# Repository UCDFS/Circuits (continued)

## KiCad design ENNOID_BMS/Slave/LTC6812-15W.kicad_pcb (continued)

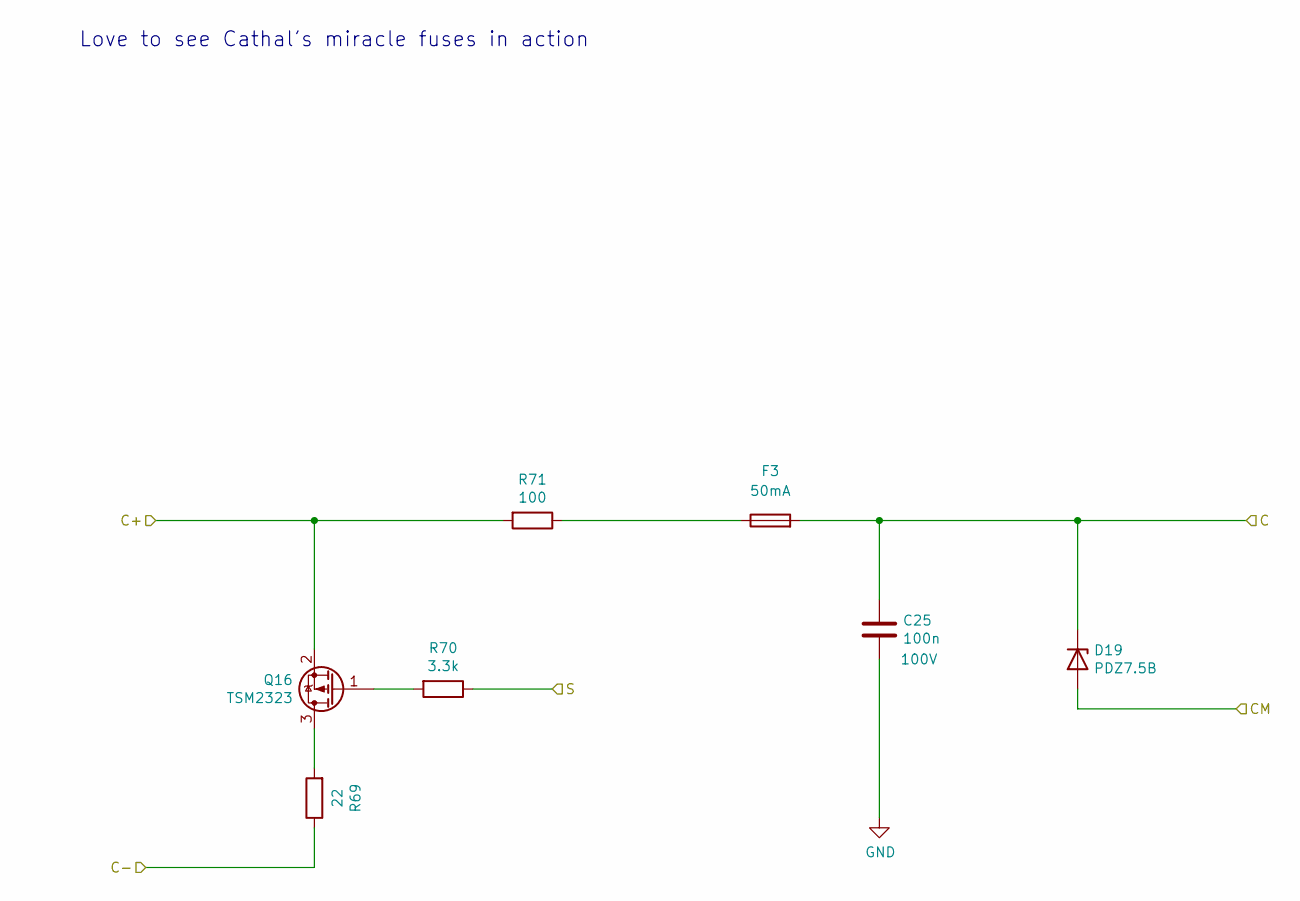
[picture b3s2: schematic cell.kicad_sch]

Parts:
C25: 100n; C_0603_1608Metric; Voltage 100V; Part Number GRM188R72A104KA35D
D19: PDZ7.5B; D_SOD-323; Part Number PDZ7.5B
F3: 50mA; Fuse_1206_3216Metric; Part Number 3413.0002.11
Q16: TSM2323; SOT-23; Part Number TSM2323CX RFG
R69: 22; R_2512_6332Metric; Part Number AC2512JK-7W22RL
R70: 3.3k; R_0508_1220Metric; Part Number WK73R2ATTD3301F
R71: 100; R_0603_1608Metric; Part Number RCS0603100RFKEA

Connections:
/cell14/C: D19.2 (A); also elsewhere on the board
/cell15/C: C25.2, D19.1 (K), F3.2; also elsewhere on the board
/cell15/S: R70.1; also elsewhere on the board
Cell_1-: C25.1; also elsewhere on the board
Cell_14+: R69.1; also elsewhere on the board
Cell_15+: Q16.2 (S), R71.2; also elsewhere on the board
unnamed: F3.1, R71.1
unnamed: Q16.3 (D), R69.2
unnamed: Q16.1 (G), R70.2

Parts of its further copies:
C11, C12, C13, C14, C15, C16, C17, C18, C19, C20, C21, C22, C23, C24: 100n; C_0603_1608Metric; Voltage 100V; Part Number GRM188R72A104KA35D
D5, D6, D7, D8, D9, D10, D11, D12, D13, D14, D15, D16, D17, D18: PDZ7.5B; D_SOD-323; Part Number PDZ7.5B
F5, F7, F9, F11, F13, F15, F20, F22, F24, F26, F28, F30, F32, F34: 50mA; Fuse_1206_3216Metric; Part Number 3413.0002.11
Q2, Q3, Q4, Q5, Q6, Q7, Q8, Q9, Q10, Q11, Q12, Q13, Q14, Q15: TSM2323; SOT-23; Part Number TSM2323CX RFG
R13, R17, R21, R25, R29, R33, R37, R41, R45, R49, R53, R57, R61, R65: 22; R_2512_6332Metric; Part Number AC2512JK-7W22RL
R14, R18, R22, R26, R30, R34, R38, R42, R46, R50, R54, R58, R62, R66: 3.3k; R_0508_1220Metric; Part Number WK73R2ATTD3301F
R15, R19, R23, R27, R31, R35, R39, R43, R47, R51, R55, R59, R63, R67: 100; R_0603_1608Metric; Part Number RCS0603100RFKEA

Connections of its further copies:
/cell1/C: C11.2, D5.1 (K), D6.2 (A), F34.2; also elsewhere on the board
/cell1/S: R14.1; also elsewhere on the board
/cell2/C: C12.2, D6.1 (K), D7.2 (A), F32.2; also elsewhere on the board
/cell2/S: R18.1; also elsewhere on the board
/cell3/C: C13.2, D7.1 (K), D8.2 (A), F30.2; also elsewhere on the board
/cell3/S: R22.1; also elsewhere on the board
/cell4/C: C14.2, D8.1 (K), D9.2 (A), F28.2; also elsewhere on the board
/cell4/S: R26.1; also elsewhere on the board
/cell5/C: C15.2, D9.1 (K), D10.2 (A), F26.2; also elsewhere on the board
/cell5/S: R30.1; also elsewhere on the board
/cell6/C: C16.2, D10.1 (K), D11.2 (A), F24.2; also elsewhere on the board
/cell6/S: R34.1; also elsewhere on the board
/cell7/C: C17.2, D11.1 (K), D12.2 (A), F22.2; also elsewhere on the board
/cell7/S: R38.1; also elsewhere on the board
/cell8/C: C18.2, D12.1 (K), D13.2 (A), F20.2; also elsewhere on the board
/cell8/S: R42.1; also elsewhere on the board
/cell9/S: R46.1; also elsewhere on the board
/cell10/C: C20.2, D14.1 (K), D15.2 (A), F13.2; also elsewhere on the board
/cell10/CM: C19.2, D13.1 (K), D14.2 (A), F15.2; also elsewhere on the board
/cell10/S: R50.1; also elsewhere on the board
/cell11/C: C21.2, D15.1 (K), D16.2 (A), F11.2; also elsewhere on the board
/cell11/S: R54.1; also elsewhere on the board
/cell12/C: C22.2, D16.1 (K), D17.2 (A), F9.2; also elsewhere on the board
/cell12/S: R58.1; also elsewhere on the board
/cell13/C: C23.2, D17.1 (K), D18.2 (A), F7.2; also elsewhere on the board
/cell13/S: R62.1; also elsewhere on the board
/cell14/C: C24.2, D18.1 (K), F5.2; also elsewhere on the board
/cell14/S: R66.1; also elsewhere on the board
Cell_1+: Q2.2 (S), R15.2, R17.1; also elsewhere on the board
Cell_1-: C11.1, C12.1, C13.1, C14.1, C15.1, C16.1, C17.1, C18.1, C19.1, C20.1, C21.1, C22.1, C23.1, C24.1, D5.2 (A), R13.1; also elsewhere on the board
Cell_2+: Q3.2 (S), R19.2, R21.1; also elsewhere on the board
Cell_3+: Q4.2 (S), R23.2, R25.1; also elsewhere on the board
Cell_4+: Q5.2 (S), R27.2, R29.1; also elsewhere on the board
Cell_5+: Q6.2 (S), R31.2, R33.1; also elsewhere on the board
Cell_6+: Q7.2 (S), R35.2, R37.1; also elsewhere on the board
Cell_7+: Q8.2 (S), R39.2, R41.1; also elsewhere on the board
Cell_8+: Q9.2 (S), R43.2, R45.1; also elsewhere on the board
Cell_9+: Q10.2 (S), R47.2, R49.1; also elsewhere on the board
Cell_10+: Q11.2 (S), R51.2, R53.1; also elsewhere on the board
Cell_11+: Q12.2 (S), R55.2, R57.1; also elsewhere on the board
Cell_12+: Q13.2 (S), R59.2, R61.1; also elsewhere on the board
Cell_13+: Q14.2 (S), R63.2, R65.1; also elsewhere on the board
Cell_14+: Q15.2 (S), R67.2; also elsewhere on the board
unnamed: F5.1, R67.1
unnamed: F7.1, R63.1
unnamed: F9.1, R59.1
unnamed: F11.1, R55.1
unnamed: F13.1, R51.1
unnamed: F15.1, R47.1
unnamed: F20.1, R43.1
unnamed: F22.1, R39.1
unnamed: F24.1, R35.1
unnamed: F26.1, R31.1
unnamed: F28.1, R27.1
unnamed: F30.1, R23.1
unnamed: F32.1, R19.1
unnamed: F34.1, R15.1
unnamed: Q2.3 (D), R13.2
unnamed: Q2.1 (G), R14.2
unnamed: Q3.3 (D), R17.2
unnamed: Q3.1 (G), R18.2
unnamed: Q4.3 (D), R21.2
unnamed: Q4.1 (G), R22.2
unnamed: Q5.3 (D), R25.2
unnamed: Q5.1 (G), R26.2
unnamed: Q6.3 (D), R29.2
unnamed: Q6.1 (G), R30.2
unnamed: Q7.3 (D), R33.2
unnamed: Q7.1 (G), R34.2
unnamed: Q8.3 (D), R37.2
unnamed: Q8.1 (G), R38.2
unnamed: Q9.3 (D), R41.2
unnamed: Q9.1 (G), R42.2
unnamed: Q10.3 (D), R45.2
unnamed: Q10.1 (G), R46.2
unnamed: Q11.3 (D), R49.2
unnamed: Q11.1 (G), R50.2
unnamed: Q12.3 (D), R53.2
unnamed: Q12.1 (G), R54.2
unnamed: Q13.3 (D), R57.2
unnamed: Q13.1 (G), R58.2
unnamed: Q14.3 (D), R61.2
unnamed: Q14.1 (G), R62.2
unnamed: Q15.3 (D), R65.2
unnamed: Q15.1 (G), R66.2

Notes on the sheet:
Love to see Cathal's miracle fuses in action

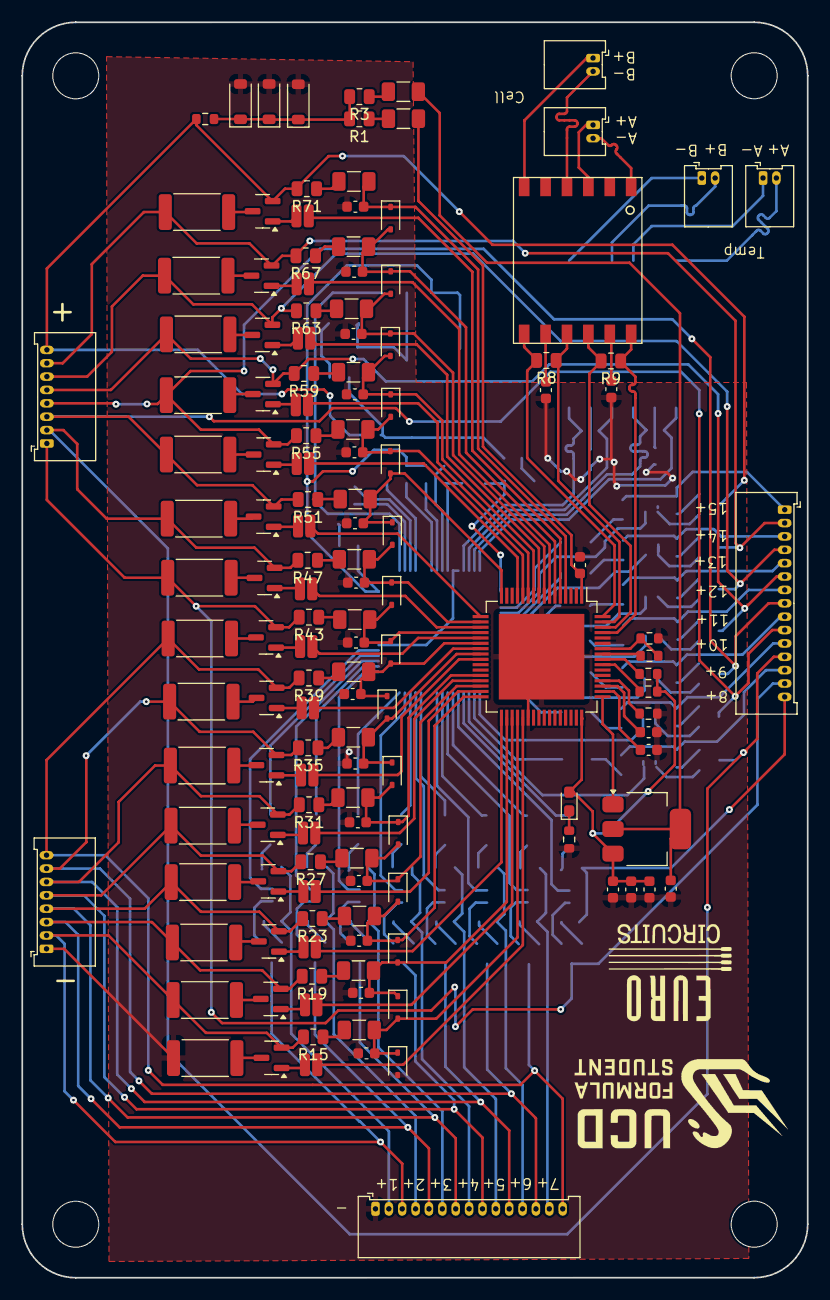
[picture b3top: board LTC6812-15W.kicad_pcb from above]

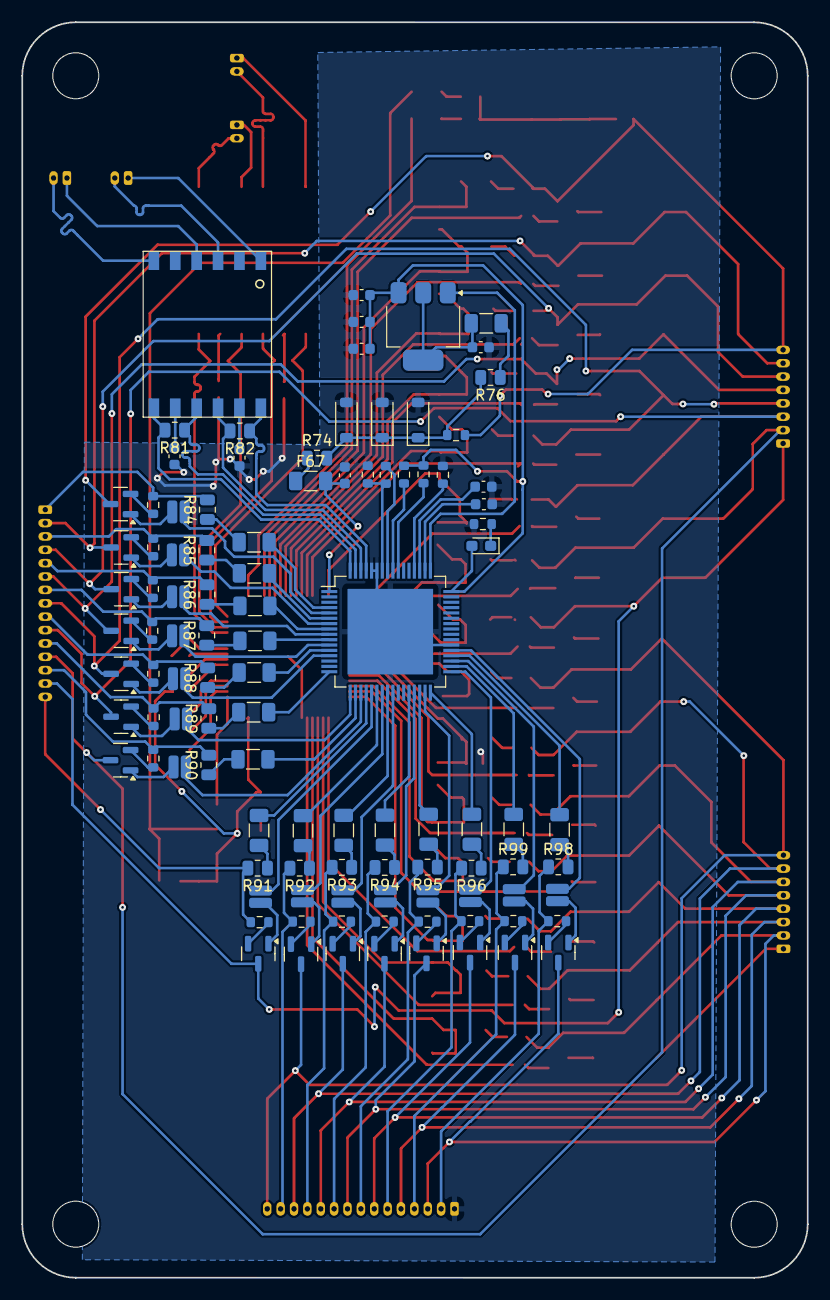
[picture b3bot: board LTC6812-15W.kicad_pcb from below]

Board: 2 copper layers, 73.4 x 117.4 mm, 246 parts (104 on the bottom side), 231 nets.

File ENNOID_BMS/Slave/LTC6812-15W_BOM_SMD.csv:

Reference,Qty,Value,DNP,Exclude from Board,Footprint,Datasheet,Part Number
"C1,C4,C10,C11,C12,C13,C14,C15,C16,C17,C18,C19,C20,C21,C22,C23,C24,C25,C28",19,100n,,,Capacitor_SMD:C_0603_1608Metric,https://pim.murata.com/asset/pim4/ceramicCapacitorSMD/GRM188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,GRM188R72A104KA35D
"C2,C3,C5,C6,C7,C26,C27,C29,C30,C31",10,1uF,,,Capacitor_SMD:C_0603_1608Metric,https://mm.digikey.com/Volume0/opasdata/d220001/medias/docus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,CL10B105KP8NNNC
"C8,C9,C32,C33",4,100p,,,Capacitor_SMD:C_0603_1608Metric,https://pim.murata.com/asset/pim4/ceramicCapacitorSMD/GRM188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,GRM1885C1H101JA01D
"D1,D2,D20,D21",4,1N4148W,,,Diode_SMD:D_SOD-123,https://www.mouser.ie/datasheet/3/175/1/BAV16W_1N4148W.pdf,1N4148W-7-F
"D3,D22",2,MMSZ5268BT1G,,,Diode_SMD:D_SOD-123,https://www.onsemi.com/pub/Collateral/MMSZ5221BT1-D.PDF,MMSZ5268BT1G
"D4,D23",2,LED,,,LED_SMD:LED_0603_1608Metric_Pad1.05x0.95mm_HandSolder,https://www.vishay.com/doc?84393,VLMTG1400-GS08
"D5,D6,D7,D8,D9,D10,D11,D12,D13,D14,D15,D16,D17,D18,D19",15,PDZ7.5B,,,Diode_SMD:D_SOD-323,https://assets.nexperia.com/documents/data-sheet/PDZ-B_SER.pdf,PDZ7.5B
"F4,F5,F6,F7,F8,F9,F10,F11,F12,F13,F14,F15,F16,F17,F18,F19",16,0.25A,,,Fuse:Fuse_0603_1608Metric,https://www.littelfuse.com/assetdocs/littelfuse_fuse_438_dat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,0438.250WR
"FB1,FB2",2,33,,,Resistor_SMD:R_0603_1608Metric,https://www.mouser.ie/datasheet/3/76/1/ENFA0003.pdf,BLM18PG330SN1D
"Q1,Q17",2,DZTT5551,,,Package_TO_SOT_SMD:SOT-223,https://www.mouser.ie/datasheet/3/175/1/ds31219.pdf,DZT5551-13
"Q2,Q3,Q4,Q5,Q6,Q7,Q8,Q9,Q10,Q11,Q12,Q13,Q14,Q15,Q16",15,TSM2323,,,Package_TO_SOT_SMD:SOT-23,https://www.taiwansemi.com/assets/datasheet/pdf.php?pn=TSM2323CX,TSM2323
"R1,R3,R8,R9,R15,R19,R23,R27,R31,R35,R39,R43,R47,R51,R55,R59,R63,R67,R71,R74,R76,R81,R82,R84,R85,R86,R87,R88,R89,R90,R91,R92,R93,R94,R95,R96,R98,R99",38,100,,,Resistor_SMD:R_0603_1608Metric,https://www.vishay.com/docs/20035/dcrcwe3.pdf,CRCW0603100RFKEA
"R2,R75",2,806,,,Resistor_SMD:R_0603_1608Metric,https://www.vishay.com/docs/20035/dcrcwe3.pdf,CRCW0603806RFKEA
"R4,R77",2,1M,,,Resistor_SMD:R_0603_1608Metric,https://www.vishay.com/docs/20035/dcrcwe3.pdf,CRCW06031M00FKEA
"R5,R10,R78,R83",4,1.2k,,,Resistor_SMD:R_0603_1608Metric,https://www.vishay.com/docs/20035/dcrcwe3.pdf,CRCW06031K20FKEA
"R6,R7,R79,R80",4,0,,,Resistor_SMD:R_0603_1608Metric,https://www.vishay.com/docs/20035/dcrcwe3.pdf,CRCW06030000Z0EA
"R11,R12,R16,R20,R24,R28,R32,R36,R40,R44,R48,R52,R56,R60,R64",15,680,,,Resistor_SMD:R_0603_1608Metric,https://www.vishay.com/docs/20035/dcrcwe3.pdf,CRCW0603680RFKEA
"R13,R17,R21,R25,R29,R33,R37,R41,R45,R49,R53,R57,R61,R65,R69",15,22,,,Resistor_SMD:R_2512_6332Metric,https://www.mouser.ie/datasheet/3/508/1/PYu-AC_51_RoHS_L_11.pdf,AC2512JK-7W22RL
"R14,R18,R22,R26,R30,R34,R38,R42,R46,R50,R54,R58,R62,R66,R70",15,3.3k,,,Resistor_SMD:R_0603_1608Metric,https://www.vishay.com/docs/20035/dcrcwe3.pdf,CRCW06033K30FKEA
"TR1,TR2",2,HM2102NL,,,ENNOID:HM2102NL,https://www.mouser.ie/datasheet/3/508/1/HM2102NL.pdf,HM2102NL
"U1,U2",2,LTC6812-1,,,ENNOID:TQFP-64-1EP_10x10mm_P0.5mm_EP8x8mm,https://www.analog.com/media/en/technical-documentation/data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,LTC6812-1

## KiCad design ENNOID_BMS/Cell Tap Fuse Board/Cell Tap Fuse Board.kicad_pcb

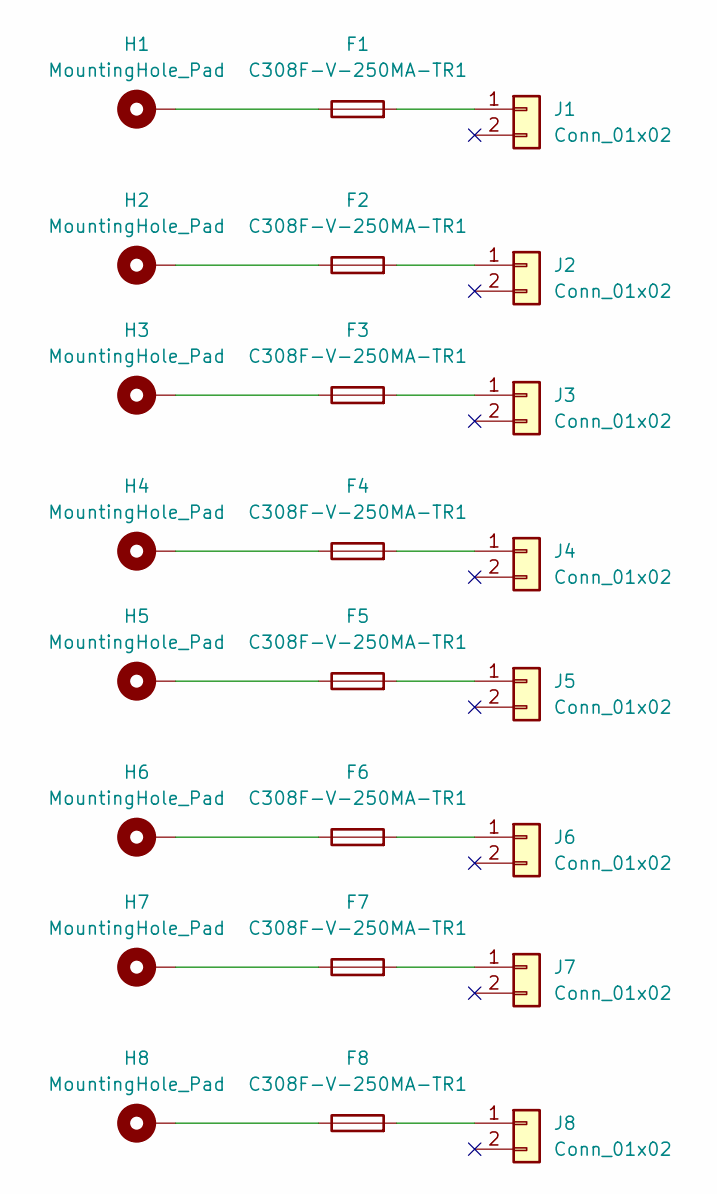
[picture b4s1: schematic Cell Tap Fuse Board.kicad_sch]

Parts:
F1, F2, F3, F4, F5, F6, F7, F8: C308F-V-250MA-TR1; MPN C308F-V-250MA-TR1
H1, H2, H3, H4, H5, H6, H7, H8: MountingHole_Pad; MountingHole_5.5mm_Pad
J1, J2, J3, J4, J5, J6, J7, J8: Conn_01x02; Molex_PicoBlade_53047-0210_1x02_P1.25mm_Vertical; MPN 53047-0210

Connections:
unnamed: F1.1, H1.1
unnamed: F2.1, H2.1
unnamed: F3.1, H3.1
unnamed: F4.1, H4.1
unnamed: F5.1, H5.1
unnamed: F6.1, H6.1
unnamed: F7.1, H7.1
unnamed: F8.1, H8.1
unnamed: F1.2, J1.1
unnamed: F2.2, J2.1
unnamed: F3.2, J3.1
unnamed: F4.2, J4.1
unnamed: F5.2, J5.1
unnamed: F6.2, J6.1
unnamed: F7.2, J7.1
unnamed: F8.2, J8.1

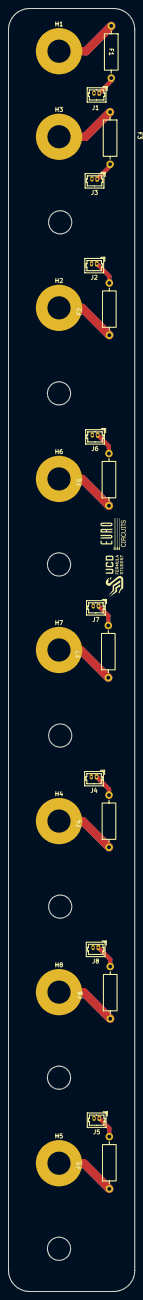
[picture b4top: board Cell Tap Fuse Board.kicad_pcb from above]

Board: 2 copper layers, 30.0 x 304.9 mm, 24 parts (0 on the bottom side), 16 nets.

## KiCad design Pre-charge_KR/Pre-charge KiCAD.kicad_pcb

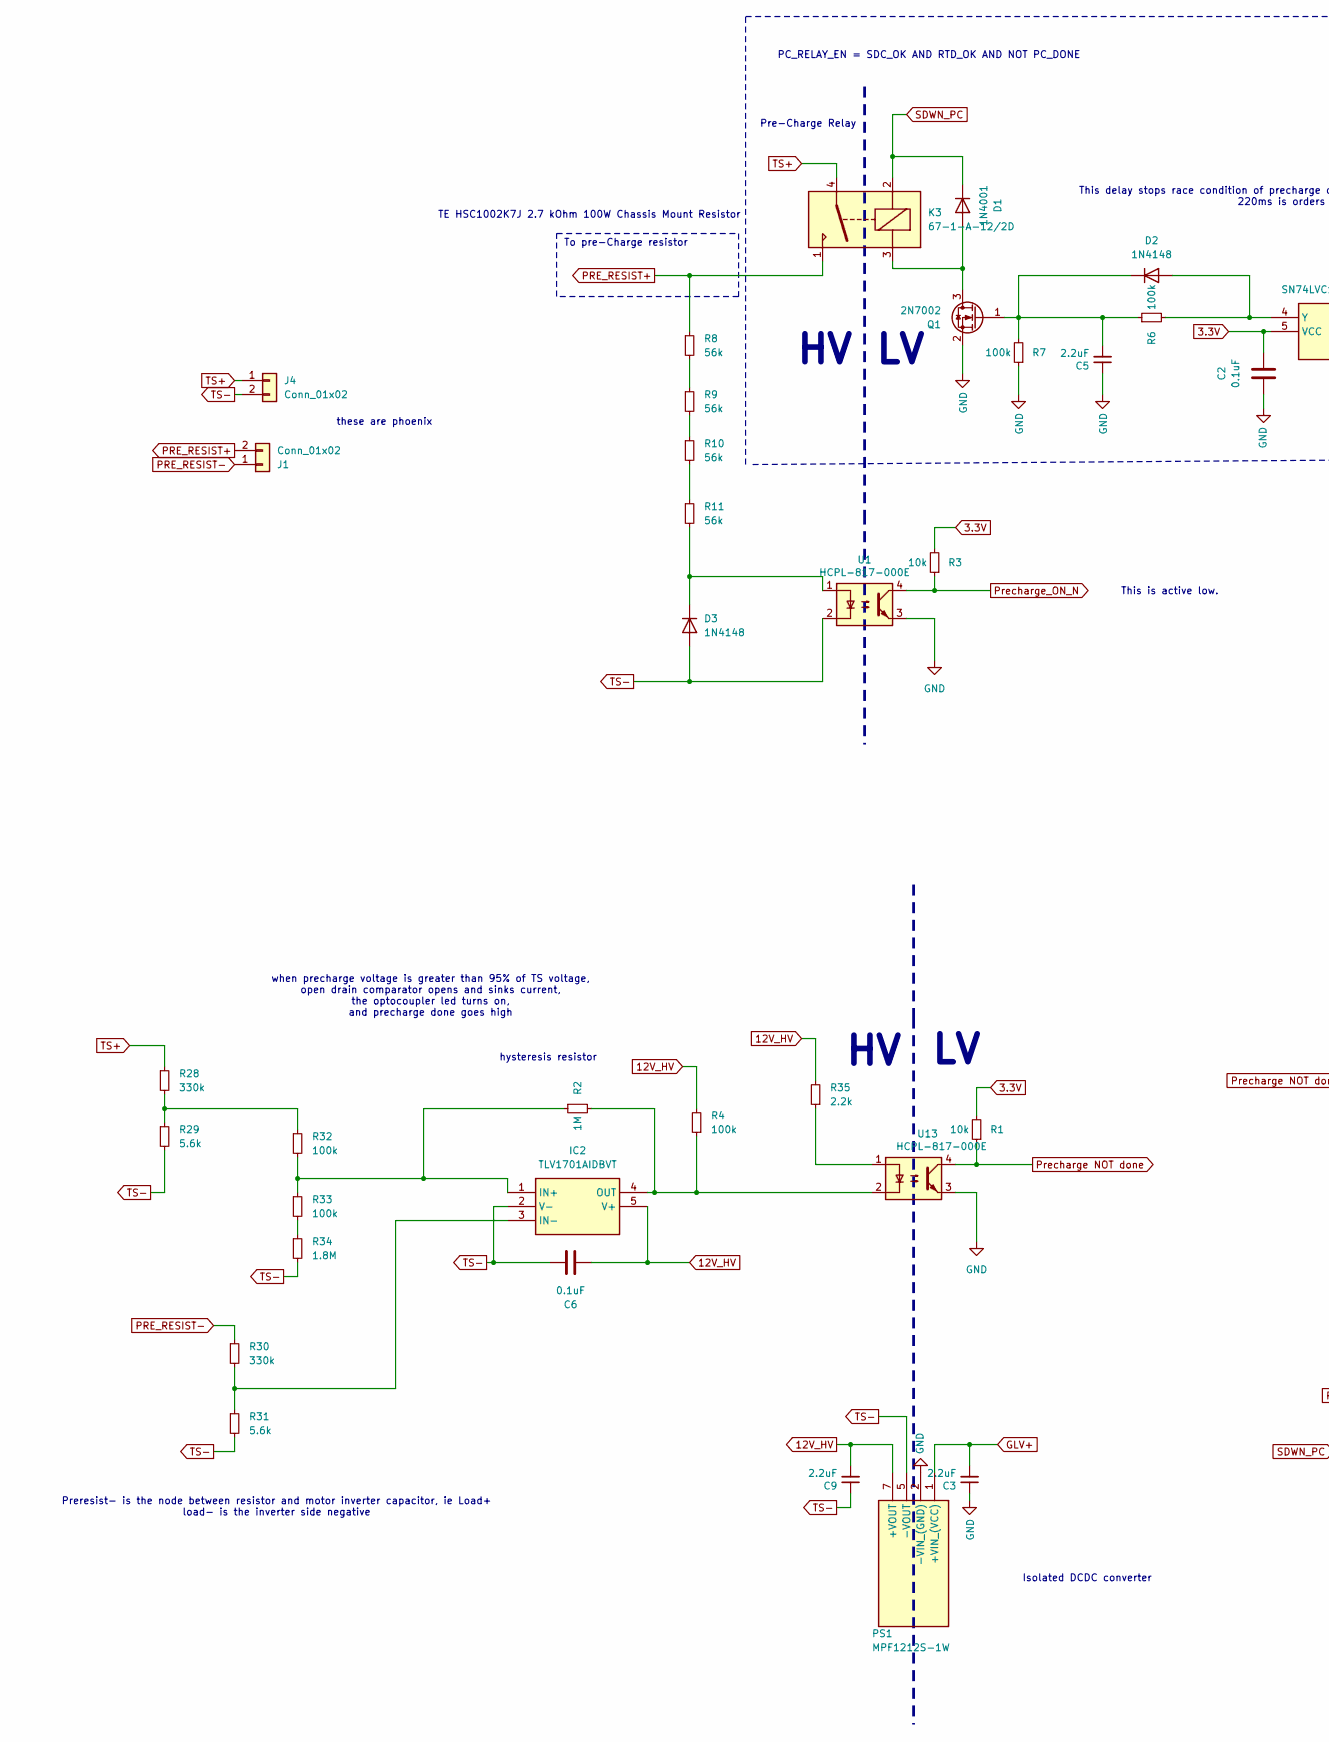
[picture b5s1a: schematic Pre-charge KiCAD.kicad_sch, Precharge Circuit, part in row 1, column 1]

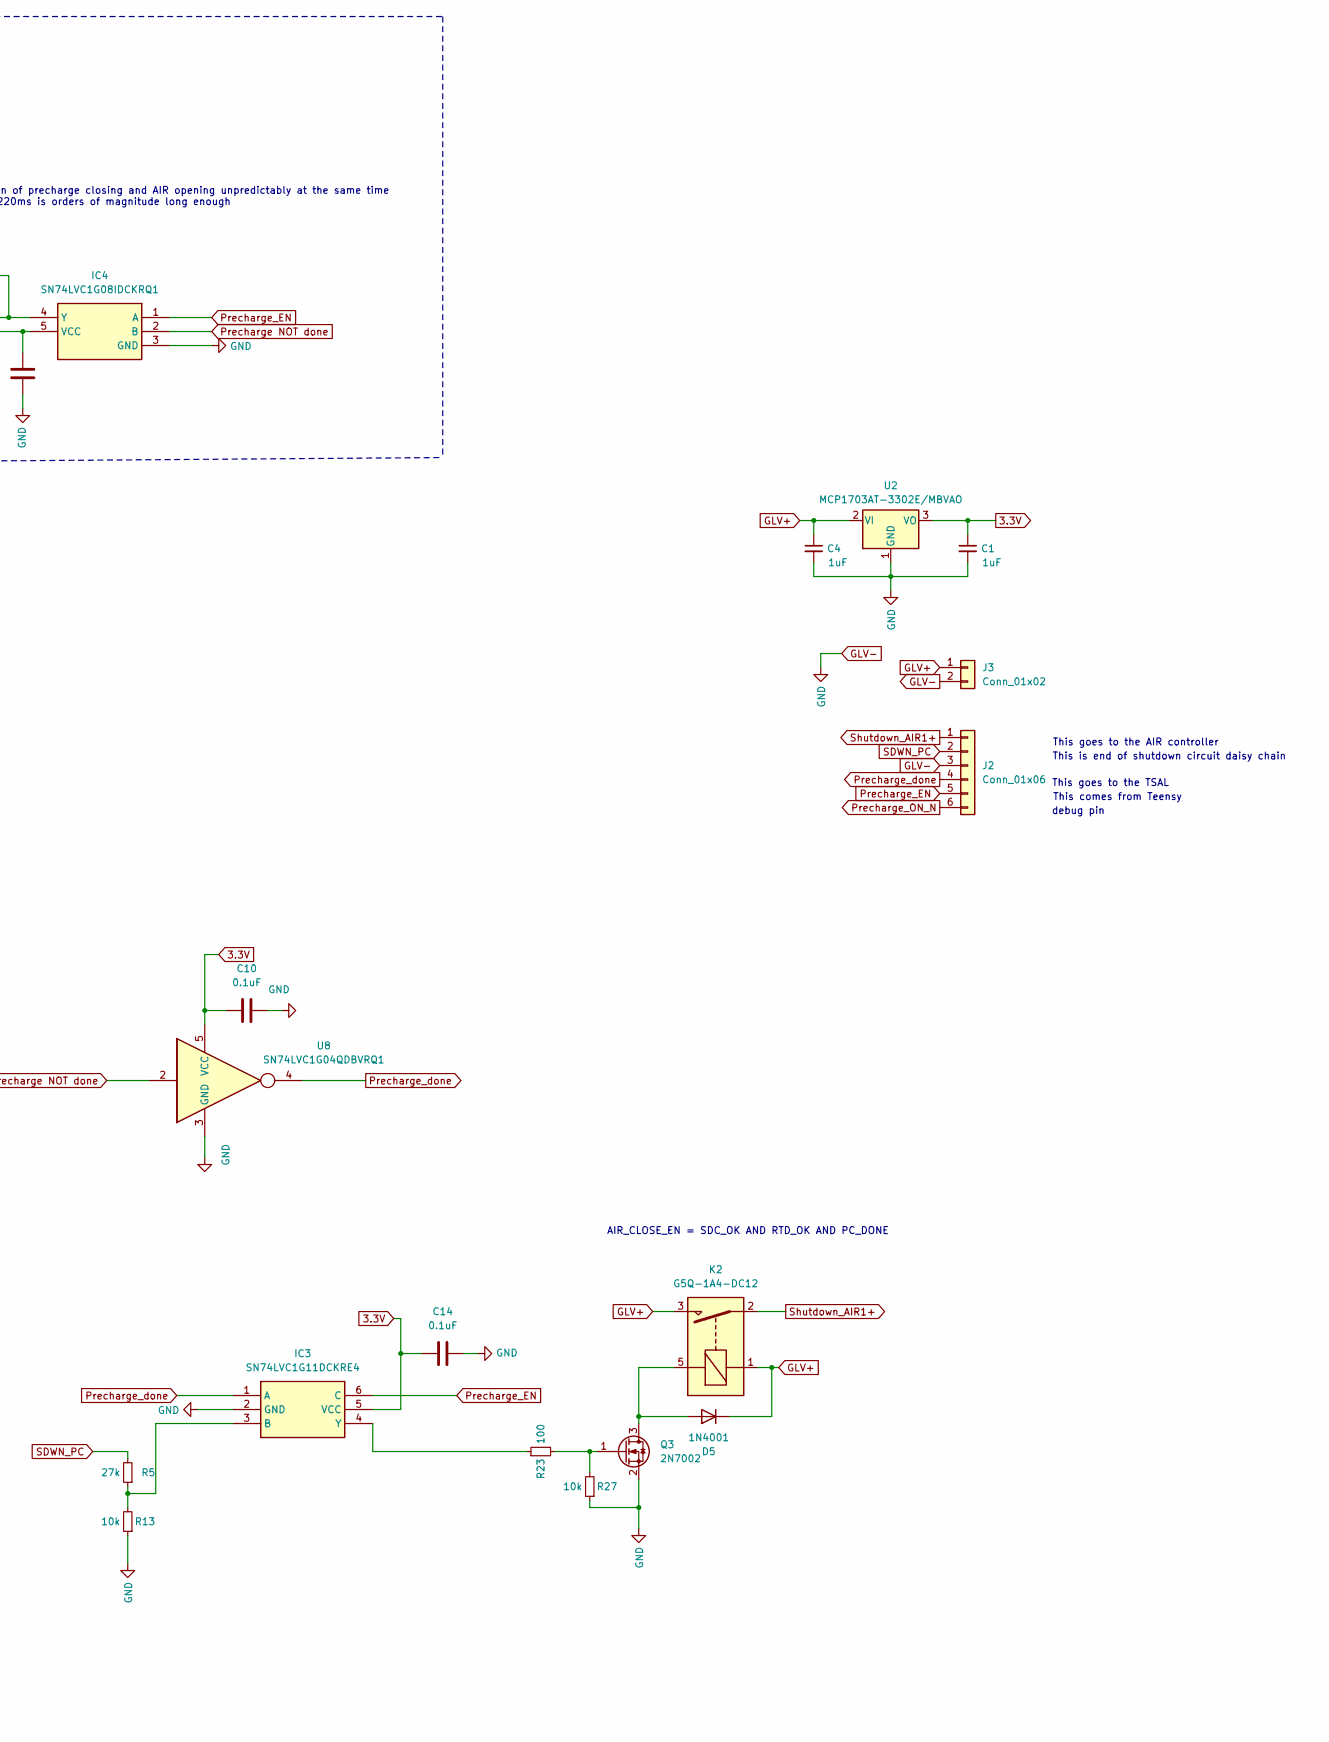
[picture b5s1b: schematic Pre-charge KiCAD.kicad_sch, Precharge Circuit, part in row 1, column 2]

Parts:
C1, C4: 1uF; FA18X7R1H104KNU00; Part Number FA18X7R1E105KRU00
C2, C6, C10, C14: 0.1uF; FA18X7R1H104KNU00; Part Number FA18X7R1H104KNU00
C3, C5, C9: 2.2uF; FA14X7R1H224KNU00; Part Number FA14X7R1H225KRU00
D1, D5: 1N4001; D_DO-41_SOD81_P10.16mm_Horizontal; Part Number 1N4001
D2, D3: 1N4148; D_DO-35_SOD27_P7.62mm_Horizontal; Part Number 1N4148
IC2: TLV1701AIDBVT; SOT95P280X145-5N; Mouser Part Number 595-TLV1701AIDBVT
IC3: SN74LVC1G11DCKRE4; SOT65P210X110-6N; Mouser Part Number 595-74LVC1G11DCKRE4
IC4: SN74LVC1G08IDCKRQ1; SOT65P210X110-5N; Mouser Part Number 595-SN74LVC1G08IDCQ1
J1, J4: Conn_01x02; Phoenix_1x2_1729128; Part Number 1729128
J2: Conn_01x06; JST_XH_B6B-XH-A_1x06_P2.50mm_Vertical; Part Number B6B-XH-A
J3: Conn_01x02; JST_XH_B2B-XH-A_1x02_P2.50mm_Vertical; Part Number B2B-XH-A
K2: G5Q-1A4-DC12; Relay_SPST_Omron-G5Q-1A; Part Number G5Q-1A4-DC12
K3: 67-1-A-12/2D; 67-1-A-12_2D; Part Number 67-1-A-12/2D
PS1: MPF1212S-1W; Part Number MPF1212S-1W
Q1, Q3: 2N7002; SOT-23; Part Number 2N7002
R1, R3, R13, R27: 10k; R_Axial_DIN0207_L6.3mm_D2.5mm_P10.16mm_Horizontal; Part Number MCF 0.25W 10K
R2: 1M; R_Axial_DIN0207_L6.3mm_D2.5mm_P10.16mm_Horizontal; Part Number MCF 0.25W 1M
R4, R6, R7, R32, R33: 100k; R_Axial_DIN0207_L6.3mm_D2.5mm_P10.16mm_Horizontal; Part Number MCF 0.25W 100K
R5: 27k; R_Axial_DIN0207_L6.3mm_D2.5mm_P10.16mm_Horizontal; Part Number MCF 0.25W 27K
R8, R9, R10, R11: 56k; R_Axial_DIN0411_L9.9mm_D3.6mm_P12.70mm_Horizontal; Part Number MCF 0.5W 56K
R23: 100; R_Axial_DIN0207_L6.3mm_D2.5mm_P10.16mm_Horizontal; Part Number MCF 0.25W 100R
R28, R30: 330k; R_Axial_DIN0411_L9.9mm_D3.6mm_P12.70mm_Horizontal; Part Number MCF 0.5W 330K
R29, R31: 5.6k; R_Axial_DIN0207_L6.3mm_D2.5mm_P10.16mm_Horizontal; Part Number MCF 0.25W 5K6
R34: 1.8M; R_Axial_DIN0207_L6.3mm_D2.5mm_P10.16mm_Horizontal; Part Number MCF 0.25W 1.8M
R35: 2.2k; R_Axial_DIN0207_L6.3mm_D2.5mm_P10.16mm_Horizontal; Part Number MCF 0.25W 2.2k
U1, U13: HCPL-817-000E; DIP-4_W7.62mm; Part Number HCPL-817-000E
U2: MCP1703AT-3302E/MBVAO; SOT-89-3; Part Number MCP1703AT-3302E/MBVAO
U8: SN74LVC1G04QDBVRQ1; SOT-23-5; Part Number SN74LVC1G04QDBVRQ1

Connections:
3.3V: C1.1, C2.1, C10.1, C14.1, IC3.5 (VCC), IC4.5 (VCC), R1.2, R3.2, U2.3 (VO), U8.5 (VCC)
12V_HV: C6.1, C9.2, IC2.5 (V+), PS1.7 (+VOUT), R4.2, R35.2
GLV+: C3.2, C4.1, D5.1 (K), J3.1, K2.1, K2.3, PS1.1 (+VIN_(VCC)), U2.2 (VI)
GLV-: C1.2, C2.2, C3.1, C4.2, C5.1, C10.2, C14.2, IC3.2 (GND), IC4.3 (GND), J2.3, J3.2, PS1.2 (-VIN_(GND)), Q1.2 (S), Q3.2 (S), R7.1, R13.1, R27.1, U1.3, U2.1 (GND), U8.3 (GND), U13.3
unnamed: D1.2 (A), K3.3, Q1.3 (D)
unnamed: D2.2 (A), IC4.4 (Y), R6.2
unnamed: C5.2, D2.1 (K), Q1.1 (G), R6.1, R7.2
unnamed: D3.1 (K), R11.2, U1.1
unnamed: D5.2 (A), K2.5, Q3.3 (D)
unnamed: IC2.1 (IN+), R2.1, R32.2, R33.1
unnamed: IC2.3 (IN-), R30.2, R31.1
unnamed: IC2.4 (OUT), R2.2, R4.1, U13.2
unnamed: IC3.3 (B), R5.1, R13.2
unnamed: IC3.4 (Y), R23.1
unnamed: Q3.1 (G), R23.2, R27.2
unnamed: R8.2, R9.1
unnamed: R9.2, R10.1
unnamed: R10.2, R11.1
unnamed: R28.2, R29.1, R32.1
unnamed: R33.2, R34.1
unnamed: R35.1, U13.1
PRE_RESIST+: J1.2, K3.1, R8.1
PRE_RESIST-: J1.1, R30.1
Precharge NOT done: IC4.2 (B), R1.1, U8.2, U13.4
Precharge_EN: IC3.6 (C), IC4.1 (A), J2.5
Precharge_ON_N: J2.6, R3.1, U1.4
Precharge_done: IC3.1 (A), J2.4, U8.4
SDWN_PC: D1.1 (K), J2.2, K3.2, R5.2
Shutdown_AIR1+: J2.1, K2.2
TS+: J4.1, K3.4, R28.1
TS-: C6.2, C9.1, D3.2 (A), IC2.2 (V-), J4.2, PS1.5 (-VOUT), R29.2, R31.2, R34.2, U1.2

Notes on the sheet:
This is end of shutdown circuit daisy chain
This goes to the TSAL
PC_RELAY_EN = SDC_OK AND RTD_OK AND NOT PC_DONE
This comes from Teensy
AIR_CLOSE_EN = SDC_OK AND RTD_OK AND PC_DONE
hysteresis resistor
This goes to the AIR controller
To pre-Charge resistor
TE HSC1002K7J 2.7 kOhm 100W Chassis Mount Resistor
Isolated DCDC converter
debug pin
when precharge voltage is greater than 95% of TS voltage, open drain comparator opens and sinks current, the optocoupler led turns on, and precharge done goes high
Preresist- is the node between resistor and motor inverter capacitor, ie Load+ load- is the inverter side negative
these are phoenix
This is active low.
This delay stops race condition of precharge closing and AIR opening unpredictably at the same time 220ms is orders of magnitude long enough
Pre-Charge Relay

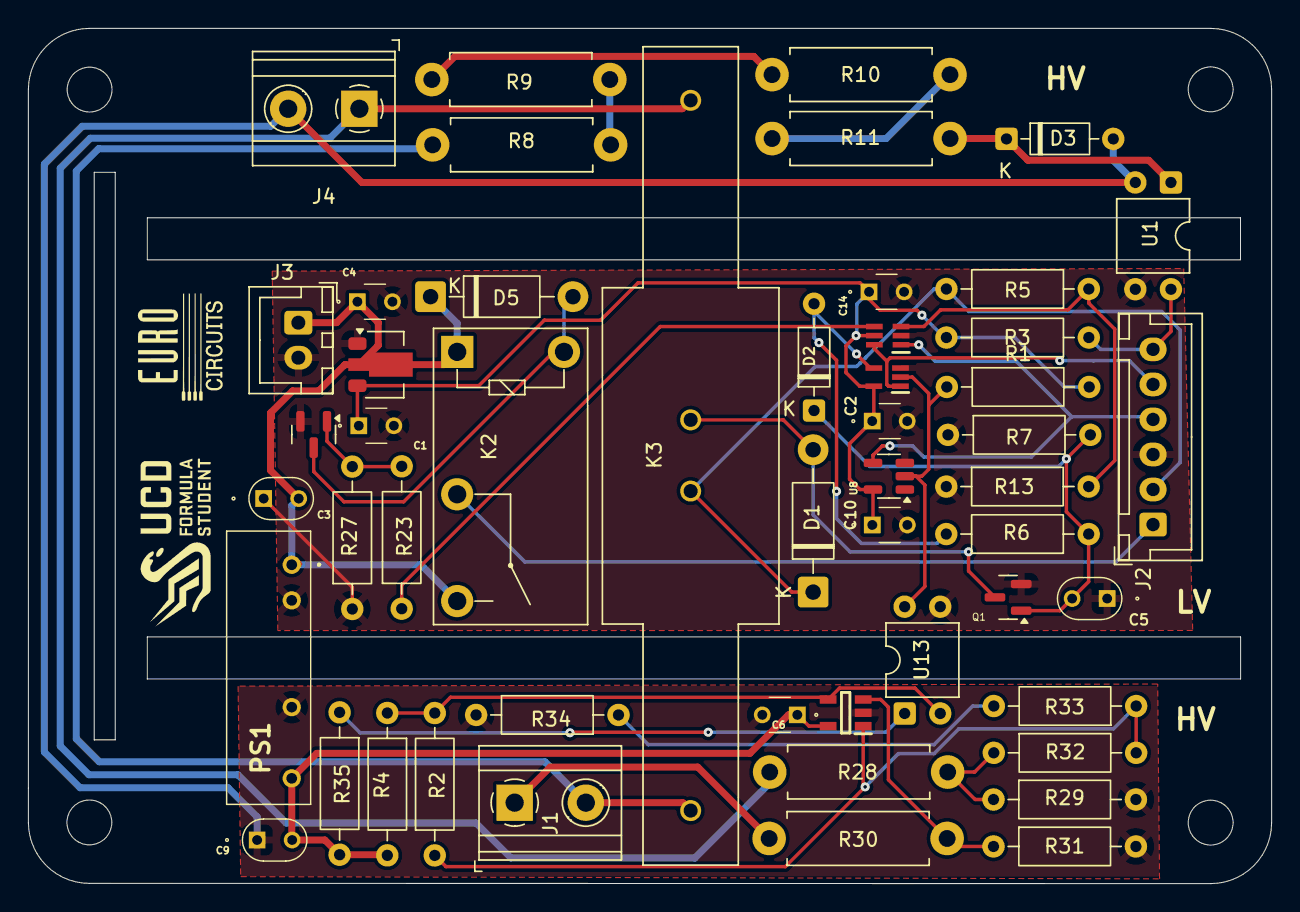
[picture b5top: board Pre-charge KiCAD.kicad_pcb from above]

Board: 2 copper layers, 88.7 x 61.0 mm, 51 parts (0 on the bottom side), 31 nets.
